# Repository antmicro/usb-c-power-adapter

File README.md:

# USB-C Power Delivery Adapter

Copyright (c) 2025 [Antmicro](https://www.antmicro.com)

## Overview

The USB-C Power Delivery Adapter is a module providing **12V 55W** continuous power output from a single [**USB-C PD**](https://www.usb.org/usb-charger-pd) power supply. 
The board was designed as a power option for [Antmicro's Thunderbolt to GPU Adapter](https://openhardware.antmicro.com/boards/thunderbolt-gpu-adapter/?tab=features) in stand-alone operation.

The design files were prepared in [KiCad 9.x](https://www.kicad.org/).

## Key features
* **12V 55W** output 
* Up to **75 Watts** achievable with active cooling
* Vishay [SIC477](https://www.vishay.com/docs/77113/sic47x.pdf) voltage buck regulator, operating at 94% efficiency
* STMicroelectronics [STUSB4500](https://www.mouser.com/datasheet/2/389/dm00489312-1799262.pdf) USB Power Delivery sink controller
* Additional **+5V** and **+3.3V** DC/DC converters delivering up to 500mA of continuous output current
* [QWIIC](https://www.sparkfun.com/qwiic) connector for programming the Power Delivery profile
* [Molex Nano-Fit](https://www.molex.com/en-us/products/connectors/wire-to-board-connectors/nano-fit-connectors) output connector
* Overload and overtemperature protection

## Configuration
To operate properly, the PD sink controller must be first programmed.\
The [QWIIC](https://www.sparkfun.com/qwiic) connector is dedicated for I2C connection with STUSB4500.\
Programming instructions and tools can be found on the [manufacturer's website](https://www.st.com/en/interfaces-and-transceivers/stusb4500.html#overview).

Below, you can find the recommended profile for the PD sink:
```console
PDO1: 5V (+15%/-5%), 1.5A
PDO2: 20.0V (+10%/-20%), 3.0A
PDO3: 20.0V (+10%/-20%), 4.5A
PDO Number: 3
Flex Current: 2.0
External Power: False
USB Communication Capable: False
Configuration OK GPIO: 2
GPIO Control: 1
Enable Power Only Above 5V: False
Request Source Current: False
Factory Default: False
```

## Operation
The USB-C Power Delivery Adapter must be powered from a USB PD power supply with the following features:
  * capable of delivering **20 V** 
  * power rating exceeding the required load ( >60 W PD supply recommended)
  * supporting at least one of the programmed PD profiles

## Project structure
* `/.` -  contains the KiCad project files, the license and this README file
* `/doc`- contains schematics in PDF format
* `/assets` - contains visual assets for showcasing this design on [Open Hardware Portal](https://openhardware.antmicro.com).

## License
The project is published under the [Apache 2.0](/LICENSE) license.

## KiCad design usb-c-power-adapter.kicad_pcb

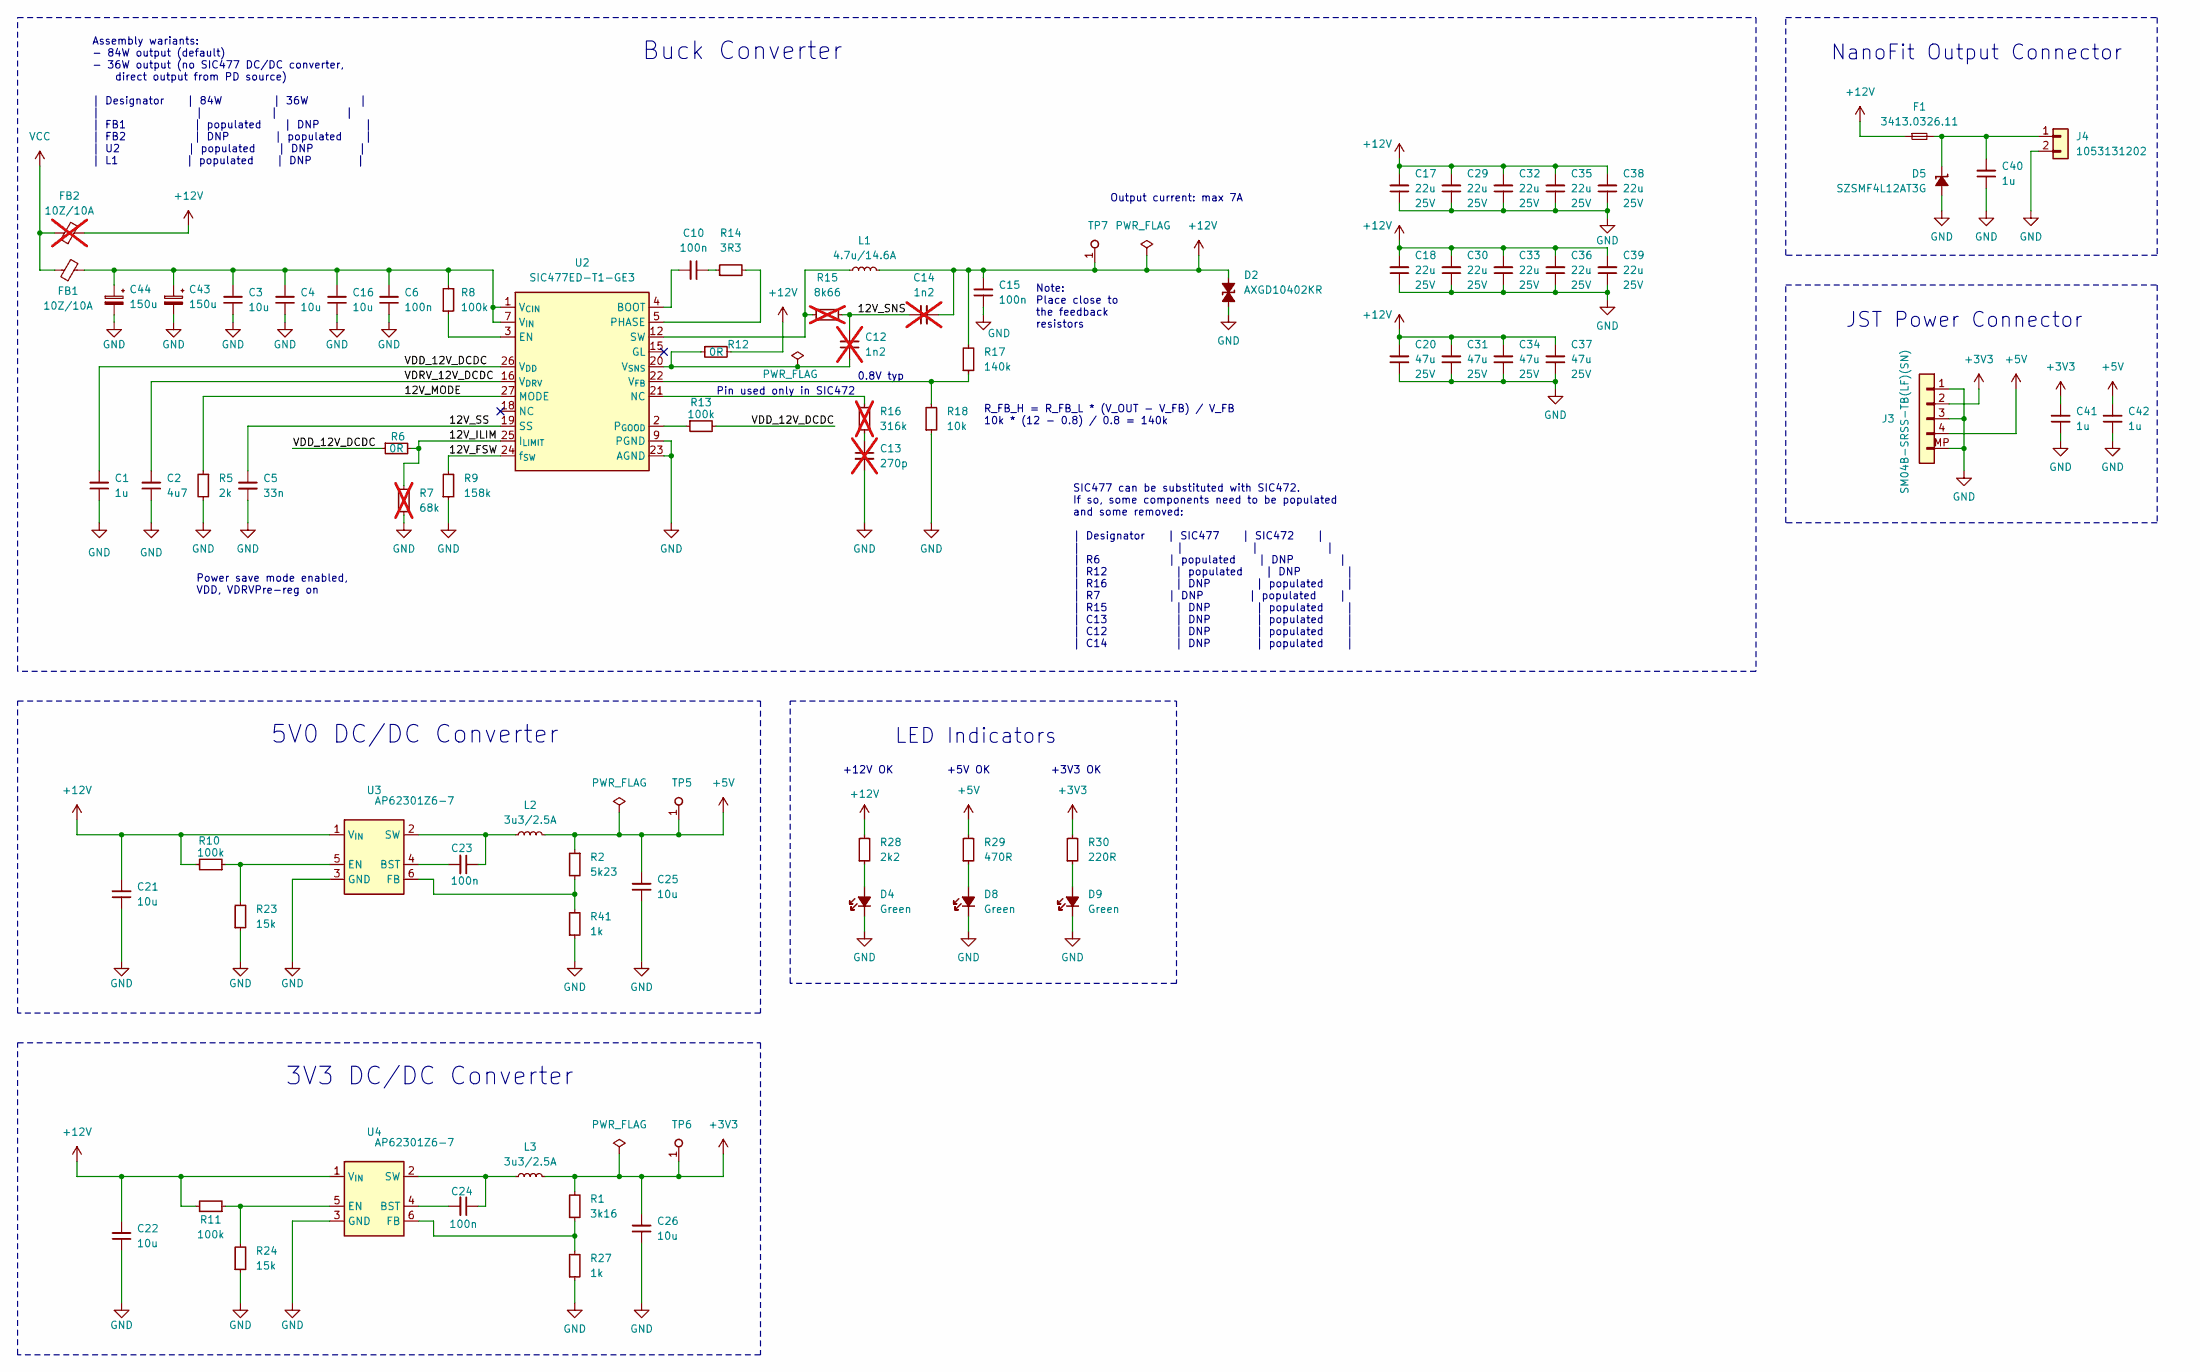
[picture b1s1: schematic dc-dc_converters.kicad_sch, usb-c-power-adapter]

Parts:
C1, C40, C41, C42: C_1u_25V_0402; C_0402_1005Metric; Voltage 25V; MPN GRM155R61E105KE11J
C2: C_4u7_25V_0402; C_0402_1005Metric; Voltage 25V; MPN GRM155C61E475ME15J
C3, C4, C16: C_10u_0805_35V; C_0805_2012Metric; Voltage 35V; MPN GRM21BR6YA106KE43L
C5: C_33n_0402; C_0402_1005Metric; MPN GCM155R71E333KA55D
C6, C10, C15, C23, C24: C_100n_50V_X8L_0402; C_0402_1005Metric; Voltage 50V; MPN GCM155L8EH104KE07D
C12, C14: C_1n2_50V_0402; C_0402_1005Metric; Voltage 50V; MPN GCM155R71H122KA37D; not fitted
C13: C_270p_25V_0402; C_0402_1005Metric; Voltage 25V; MPN C0402C271J3GAC7867; not fitted
C17, C18, C29, C30, C32, C33, C35, C36, C38, C39: C_22u_25V_0805; C_0805_2012Metric; Voltage 25V; MPN CL21A226MAYNNNE
C20, C31, C34, C37: C_47u_25V_1206; C_1206_3216Metric; Voltage 25V; MPN C3216X5R1E476M160AC
C21, C22, C25, C26: C_10u_25V_0603; C_0603_1608Metric; Voltage 25V; MPN C1608X5R1E106M080AC
C43, C44: C_Pol_150u_30V_Vishay-T59-EE; C_Pol_Vishay-T59-EE; Voltage 30V; MPN T59EE157M030C0075
D2: AXGD10402KR; D_0402_1005Metric; MPN AXGD10402KR
D4, D8, D9: LED_G_0603_LG_L29K-G2J1-24-Z; LED_0603_1608Metric_G; MPN LG L29K-G2J1-24-Z
D5: SZSMF4L12AT3G; SOD-123FL; MPN SZSMF4L12AT3G
F1: F_7A_1206; F_1206_3216Metric; MPN 3413.0326.11
FB1: FB_10Z_10A_WE-MPSB_1206; FB_1206_3216Metric; MPN 74279221100
FB2: FB_10Z_10A_WE-MPSB_1206; FB_1206_3216Metric; MPN 74279221100; not fitted
J3: JST_SH_1x4_SM04B-SRSS-TB-LF-SN; Conn_JST_SH_1x4_SM04B-SRSS-TB-LF-SN; MPN SM04B-SRSS-TB(LF)(SN)
J4: Molex_Nano-Fit_1x2_1053131202; Conn_Molex_Nano-Fit_1x2_1053131102; MPN 1053131202
L1: L_4u7_14.6A_Abracon-Q8080; L_Abracon_ASPIAIG-Q8080; MPN ASPIAIG-Q8080-4R7M-T
L2, L3: L_3u3_2.5A_1008; L_1008_2520Metric; MPN TFM252012ALMA3R3MTAA
R1: R_3k16_0402; R_0402_1005Metric; Tolerance 1%; MPN RC0402FR-073K16L
R2: R_5k23_0402; R_0402_1005Metric; Tolerance 1%; MPN RC0402FR-075K23L
R5: R_2k_0402; R_0402_1005Metric; Tolerance 1%; MPN CR0402-FX-2001GLF
R6, R12: R_0R_0402; R_0402_1005Metric; MPN ERJ2GE0R00X
R7: R_68k_0402; R_0402_1005Metric; Tolerance 1%; MPN CR0402-FX-6802GLF; not fitted
R8, R10, R11, R13: R_100k_0402; R_0402_1005Metric; Tolerance 1%; MPN CR0402-FX-1003GLF
R9: R_158k_0402; R_0402_1005Metric; Tolerance 1%; MPN CR0402-FX-1583GLF
R14: R_3R3_0402; R_0402_1005Metric; Tolerance 1%; MPN CR0402-FX-3R30GLF
R15: R_8k66_0402; R_0402_1005Metric; Tolerance 1%; MPN CR0402-FX-8661GLF; not fitted
R16: R_316k_0402; R_0402_1005Metric; Tolerance 1%; MPN CR0402-FX-3163GLF; not fitted
R17: R_140k_0.1%_0402; R_0402_1005Metric; Tolerance 0.1%; MPN RT0402BRD07140KL
R18: R_10k_0.1%_0402; R_0402_1005Metric; Tolerance 0.1%; MPN CRT0402-BY-1002GLF
R23, R24: R_15k_0402; R_0402_1005Metric; Tolerance 1%; MPN CR0402-FX-1502GLF
R27, R41: R_1k_0402; R_0402_1005Metric; Tolerance 1%; MPN CR0402-FX-1001GLF
R28: R_2k2_0402; R_0402_1005Metric; Tolerance 1%; MPN CR0402-FX-2201GLF
R29: R_470_0402; R_0402_1005Metric; Tolerance 1%; MPN CR0402-FX-4700GLF
R30: R_220R_0402; R_0402_1005Metric; Tolerance 1%; MPN CR0402-FX-2200GLF
TP5, TP6, TP7: TP_0.75mm_SMD; TP_SMD_0.75mm
U2: SIC477ED-T1-GE3; SIC47XED-T1-GE3; MPN SIC477ED-T1-GE3
U3, U4: AP62301Z6-7; SOT-563; MPN AP62301Z6-7

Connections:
+3V3: C26.2, C41.2, J3.2, L3.2, R1.2, R30.2, TP6.1; also elsewhere on the board
+5V: C25.2, C42.2, J3.4, L2.2, R2.1, R29.2, TP5.1; also elsewhere on the board
+12V: C14.2, C15.2, C17.2, C18.2, C20.2, C21.2, C22.2, C29.2, C30.2, C31.2, C32.2, C33.2, C34.2, C35.2, C36.2, C37.2, C38.2, C39.2, D2.2 (A), F1.1, FB2.2, L1.2, R10.2, R11.2, R12.2, R17.2, R28.2, TP7.1, U3.1 (V_{IN}), U4.1 (V_{IN})
/DC-DC Converters/12V_FSW: R9.2, U2.24 (f_{SW})
/DC-DC Converters/12V_ILIM: R6.2, R7.2, U2.25 (I_{LIMIT})
/DC-DC Converters/12V_MODE: R5.1, U2.27 (MODE)
/DC-DC Converters/12V_SNS: C12.2, C14.1, R15.2
/DC-DC Converters/12V_SS: C5.1, U2.19 (SS)
/DC-DC Converters/VDD_12V_DCDC: C1.2, R6.1, R13.2, U2.26 (V_{DD})
/DC-DC Converters/VDRV_12V_DCDC: C2.2, U2.16 (V_{DRV})
GND: C1.1, C2.1, C3.1, C4.1, C5.2, C6.1, C13.2, C15.1, C16.1, C17.1, C18.1, C20.1, C21.1, C22.1, C25.1, C26.1, C29.1, C30.1, C31.1, C32.1, C33.1, C34.1, C35.1, C36.1, C37.1, C38.1, C39.1, C40.1, C41.1, C42.1, C43.2, C44.2, D2.1 (C), D4.1 (C), D5.2 (A), D8.1 (C), D9.1 (C), J3.1, J3.3, J3.MP, J4.2, R5.2, R7.1, R9.1, R18.1, R23.1, R24.1, R27.1, R41.1, U2.9 (PGND), U2.10 (PGND), U2.11 (PGND), U2.17 (PGND), U2.23 (AGND), U2.28 (AGND), U3.3 (GND), U4.3 (GND); also elsewhere on the board
unnamed: C10.1, R14.1
unnamed: C13.1, R16.2
unnamed: D4.2 (A), R28.1
unnamed: C40.2, D5.1 (C), F1.2, J4.1
unnamed: D8.2 (A), R29.1
unnamed: D9.2 (A), R30.1
unnamed: L1.1, R15.1, U2.12 (SW), U2.13 (SW), U2.14 (SW)
unnamed: R14.2, U2.5 (PHASE), U2.6 (PHASE)
unnamed: R16.1, U2.21 (NC)
unnamed: C10.2, U2.4 (BOOT)
unnamed: R8.1, U2.3 (EN)
unnamed: R13.1, U2.2 (P_{GOOD})
unnamed: C3.2, C4.2, C6.2, C16.2, C43.1, C44.1, FB1.2, R8.2, U2.1 (V_{CIN}), U2.7 (V_{IN}), U2.8 (V_{IN})
unnamed: R17.1, R18.2, U2.22 (V_{FB})
unnamed: C12.1, R12.1, U2.20 (V_{SNS})
unnamed: C23.2, U3.4 (BST)
unnamed: R10.1, R23.2, U3.5 (EN)
unnamed: R2.2, R41.2, U3.6 (FB)
unnamed: C23.1, L2.1, U3.2 (SW)
unnamed: C24.2, U4.4 (BST)
unnamed: R11.1, R24.2, U4.5 (EN)
unnamed: R1.1, R27.2, U4.6 (FB)
unnamed: C24.1, L3.1, U4.2 (SW)
VCC: FB1.1, FB2.1; also elsewhere on the board

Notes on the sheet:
Note: Place close to the feedback resistors
Power save mode enabled, VDD, VDRVPre-reg on
+5V OK
R_FB_H = R_FB_L * (V_OUT - V_FB) / V_FB 10k * (12 - 0.8) / 0.8 = 140k
0.8V typ
+12V OK
Buck Converter
SIC477 can be substituted with SIC472. If so, some components need to be populated and some removed: | Designator | SIC477 | SIC472 | | | | | | R6 | populated | DNP | | R12 | populated | DNP | | R16 | DNP | populated | | R7 | DNP | populated | | R15 | DNP | populated | | C13 | DNP | populated | | C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
LED Indicators
5V0 DC/DC Converter
Pin used only in SIC472
3V3 DC/DC Converter
Assembly wariants: - 84W output (default) - 36W output (no SIC477 DC/DC converter, direct output from PD source) | Designator | 84W | 36W | | | | | | FB1 | populated | DNP | | FB2 | DNP | populated | | U2 | populated | DNP | | L1 | populated | DNP |
JST Power Connector
NanoFit Output Connector
Output current: max 7A
+3V3 OK

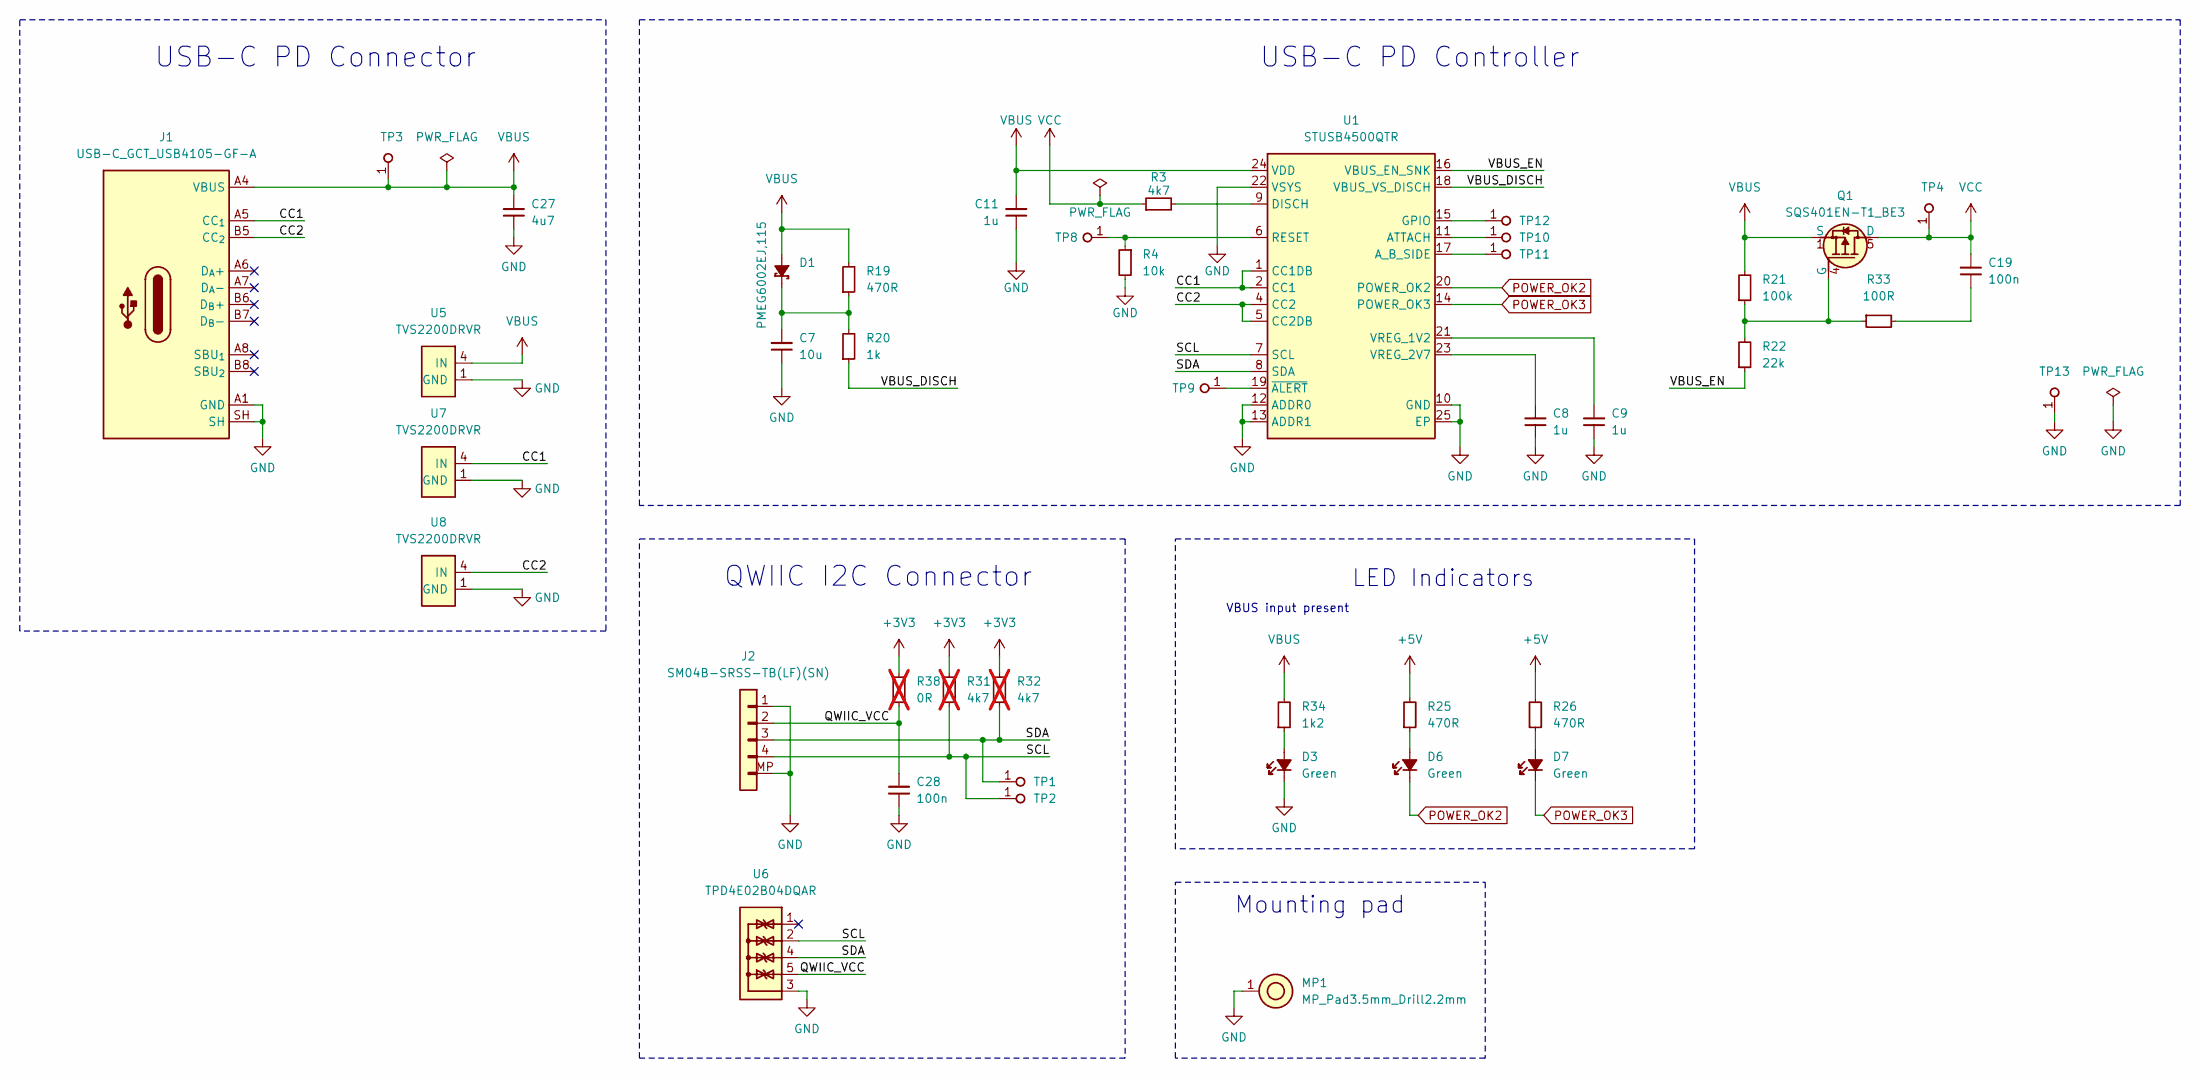
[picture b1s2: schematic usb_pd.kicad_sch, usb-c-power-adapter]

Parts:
C7: C_10u_0805_35V; C_0805_2012Metric; Voltage 35V; MPN GRM21BR6YA106KE43L
C8, C9, C11: C_1u_25V_0402; C_0402_1005Metric; Voltage 25V; MPN GRM155R61E105KE11J
C19, C28: C_100n_50V_X8L_0402; C_0402_1005Metric; Voltage 50V; MPN GCM155L8EH104KE07D
C27: C_4u7_25V_0402; C_0402_1005Metric; Voltage 25V; MPN GRM155C61E475ME15J
D1: PMEG6002EJ,115; D_SOD-323F; MPN PMEG6002EJ,115
D3, D6, D7: LED_G_0603_LG_L29K-G2J1-24-Z; LED_0603_1608Metric_G; MPN LG L29K-G2J1-24-Z
J1: USB-C_GCT_USB4105-GF-A; USB-C_Receptacle_GCT_USB4105-GF-A; MPN USB4105-GF-A
J2: JST_SH_1x4_SM04B-SRSS-TB-LF-SN; Conn_JST_SH_1x4_SM04B-SRSS-TB-LF-SN; MPN SM04B-SRSS-TB(LF)(SN)
MP1: MP_Pad3.5mm_Drill2.2mm
Q1: SQS401EN-T1_BE3; Vishay_PowerPAK_1212-8_Single; MPN SQS401EN-T1_BE3
R3: R_4k7_0603; R_0603_1608Metric; Tolerance 1%; MPN CR0603-FX-4701ELF
R4: R_10k_0402; R_0402_1005Metric; Tolerance 1%; MPN CR0402-FX-1002GLF
R19, R25: R_470R_0402; R_0402_1005Metric; Tolerance 1%; MPN CR0402-FX-4700GLF
R20: R_1k_0402; R_0402_1005Metric; Tolerance 1%; MPN CR0402-FX-1001GLF
R21: R_100k_0402; R_0402_1005Metric; Tolerance 1%; MPN CR0402-FX-1003GLF
R22: R_22k_0402; R_0402_1005Metric; Tolerance 1%; MPN CR0402-FX-2202GLF
R26: R_470_0402; R_0402_1005Metric; Tolerance 1%; MPN CR0402-FX-4700GLF
R31, R32: R_4k7_0402; R_0402_1005Metric; Tolerance 1%; MPN CR0402-FX-4701GLF; not fitted
R33: R_100R_0402; R_0402_1005Metric; Tolerance 1%; MPN CR0402-FX-1000GLF
R34: R_1k2_0402; R_0402_1005Metric; Tolerance 1%; MPN CR0402-FX-1201GLF
R38: R_0R_0402; R_0402_1005Metric; MPN ERJ2GE0R00X; not fitted
TP1, TP2, TP3, TP4, TP8, TP9, TP10, TP11, TP12, TP13: TP_0.75mm_SMD; TP_SMD_0.75mm
U1: STUSB4500_QFN; QFN-24-1EP_4x4mm_P0.5_EP2.1x2.1mm; MPN STUSB4500QTR
U5, U7, U8: TVS2200DRVR; WSON-6-1EP_2x2mm_P0.65mm; MPN TVS2200DRVR
U6: TPD4E02B04DQA; USON-10_2.5x1mm_P0.5mm; MPN TPD4E02B04DQAR

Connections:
+3V3: R31.2, R32.2, R38.2; also elsewhere on the board
+5V: R25.2, R26.2; also elsewhere on the board
/USB PD/CC1: J1.A5 (CC_{1}), U1.1 (CC1DB), U1.2 (CC1), U7.4 (IN), U7.5 (IN), U7.6 (IN)
/USB PD/CC2: J1.B5 (CC_{2}), U1.4 (CC2), U1.5 (CC2DB), U8.4 (IN), U8.5 (IN), U8.6 (IN)
/USB PD/QWIIC_VCC: C28.2, J2.2, R38.1, U6.5, U6.6
/USB PD/SCL: J2.4, R31.1, TP2.1, U1.7 (SCL), U6.2, U6.9
/USB PD/SDA: J2.3, R32.1, TP1.1, U1.8 (SDA), U6.4, U6.7
/USB PD/VBUS_DISCH: R20.1, U1.18 (VBUS_VS_DISCH)
/USB PD/VBUS_EN: R22.1, U1.16 (VBUS_EN_SNK)
GND: C7.1, C8.1, C9.1, C11.1, C27.1, C28.1, D3.1 (C), J1.A1 (GND), J1.A12 (GND), J1.B1 (GND), J1.B12 (GND), J1.SH, J2.1, J2.MP, MP1.1, R4.2, TP13.1, U1.10 (GND), U1.12 (ADDR0), U1.13 (ADDR1), U1.22 (VSYS), U1.25 (EP), U5.1 (GND), U5.2 (GND), U5.3 (GND), U5.7 (GND), U6.3, U6.8, U7.1 (GND), U7.2 (GND), U7.3 (GND), U7.7 (GND), U8.1 (GND), U8.2 (GND), U8.3 (GND), U8.7 (GND); also elsewhere on the board
unnamed: C19.1, R33.2
unnamed: C7.2, D1.1 (C), R19.1, R20.2
unnamed: D3.2 (A), R34.1
unnamed: D6.2 (A), R25.1
unnamed: D7.2 (A), R26.1
unnamed: Q1.4 (G), R21.1, R22.2, R33.1
unnamed: TP10.1, U1.11 (ATTACH)
unnamed: TP11.1, U1.17 (A_B_SIDE)
unnamed: R3.2, U1.9 (DISCH)
unnamed: TP12.1, U1.15 (GPIO)
unnamed: R4.1, TP8.1, U1.6 (RESET)
unnamed: C9.2, U1.21 (VREG_1V2)
unnamed: C8.2, U1.23 (VREG_2V7)
unnamed: TP9.1, U1.19 (~ALERT)
POWER_OK2: D6.1 (C), U1.20 (POWER_OK2)
POWER_OK3: D7.1 (C), U1.14 (POWER_OK3)
VBUS: C11.2, C27.2, D1.2 (A), J1.A4 (VBUS), J1.A9 (VBUS), J1.B4 (VBUS), J1.B9 (VBUS), Q1.1 (S), Q1.2 (S), Q1.3 (S), R19.2, R21.2, R34.2, TP3.1, U1.24 (VDD), U5.4 (IN), U5.5 (IN), U5.6 (IN)
VCC: C19.2, Q1.5 (D), R3.1, TP4.1; also elsewhere on the board

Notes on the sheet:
USB-C PD Controller
LED Indicators
VBUS input present
Mounting pad
QWIIC I2C Connector
USB-C PD Connector

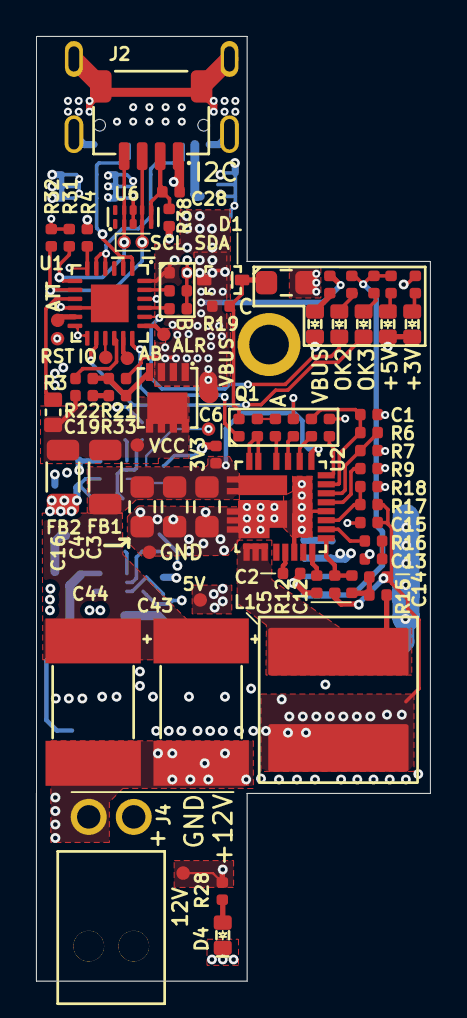
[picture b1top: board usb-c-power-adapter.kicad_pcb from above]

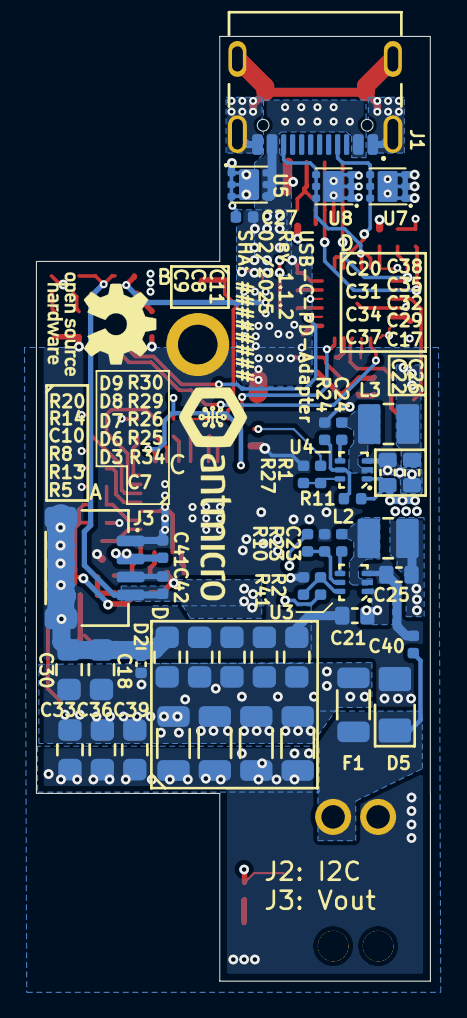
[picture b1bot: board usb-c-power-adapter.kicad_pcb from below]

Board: 4 copper layers, 21.9 x 52.5 mm, 124 parts (46 on the bottom side), 59 nets.

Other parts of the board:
N1: antmicro_logo; antmicro-logo_scaled_12mm_silk
N2: oshw_logo; OSHW-Logo_5.7x6mm_SilkScreen

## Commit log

2024-03-25 [#57006] Initial comit
2024-03-25 [#57006] Add USB-C connector
2024-03-25 [#57006] Add qwiic connector
2024-03-25 [#57006] Add Buck converter
2024-03-25 [#57006] Add USB PD controller
2024-03-25 [#57006] Update schematic
2024-03-27 [#57006] Swap I2C lines
    Align to grid
    Add notes
2024-03-27 [#57006] Change buck converter to SIC477ED-T1-GE3, WIP
2024-03-27 [#57006] Change feedback resistors
2024-03-28 [#57006] Update connections
    Change nanofit connector
    Change feedback resistors to 0.1%
2024-03-28 [#57006] Change C13, C14, C16
    Use capactitors rated for higher voltages
2024-03-28 [#57006] Add 3v3 and 5v dcdc converters
2024-03-28 [#57006] Move connectors to separate sheet
2024-03-28 [#57006] Change C17, R25, R26
    Improve connections
2024-03-28 [#57006] Add assembly variant selector
2024-03-28 [#57006] Change L1
2024-03-29 [#57006] Add a TVS diode on output
    Move power components to a new sheet
2024-03-29 [#57006] Align components to grid
2024-03-29 [#57006] Reorganize structure
2024-03-29 [#57006] Clean ERC warnings
2024-03-29 [#57006] Add LEDs on POWER_GOOD signals
2024-03-29 [#57006] Update symbols
2024-04-02 [#57006] Rename power supply sheet
2024-04-02 [#57006] Add web address
2024-04-02 [#57006] Add full date
2024-04-02 [#57006] Add 0R resistor on 3v3 qwiic
2024-04-02 [#57006] Add LEDs on 3v3 and 5v output
2024-04-02 [#57006] Improve SIC472/SIC477 assembly variants note
    Align components
2024-04-02 [#57006] Change power output variant selector
    Use ferrites instead of resistors
2024-04-02 [#57006] Remove buses to improve readability
    Change output power block's name
2024-04-02 [#57006] Change feedback resistors for U3, U4
2024-04-02 [#57006] Change D5 to SZSMF4L12AT3G
2024-04-02 [#57006] Remove fuse on VBUS input
2024-04-02 [#57006] Change diodes' resistors
    Decrease current
2024-04-02 [#57006] Fix wrong power label
    Add +12V testpoint
2024-04-02 [#57006] Remove R11, C8
2024-04-02 [#57006] Add val field to F1
2024-04-02 [#57006] Change EN resistors for U3, U4
2024-04-02 [#57006] Change R20 to 1k
    Move some components to improve readability
2024-04-04 [#57006] Mark R31, R32 as non DNP
    To avoid I2C lines floating
2024-04-04 [#57006] Add logos
2024-04-04 [#57006] Change capacitors to higher voltage ratings
    Homogenize capacitors (to not use multiple versions of the same params)
2024-04-04 [#57006] Change Rfsw to 158k
2024-04-04 [#57006] Change R3 to 0603
2024-04-04 [#57006] Change U3 U4 to SOT-563
2024-04-04 [#57006] Fix POWER_OK2, POWER_OK3 LEDs
2024-04-04 [#57006] Change D2 to AXGD10402KR
2024-04-04 [#57006] Add more testpoints
2024-04-04 [#57006] Change R7 to 68k
2024-04-04 [#57006] Add tranzistor on D3
    PD input present LED
2024-04-04 [#57006] Remove tranzistor on D3
    Change LED resistor's value
2024-04-04 [#57006] Add TVS2200DRVR on PD input
2024-04-04 [#57006] Remove PGOOD label
2024-04-04 [#57006] Change L2 and L3
2024-04-04 [#57006] Update SIC477 from library
    Add note about NC pin 21
2024-04-04 [#57006] Change C17, C18, C20 to 25V capacitors
2024-04-04 [#57006] Add 100u DNP capacitor
2024-04-04 [#57006] Update PCB from schematics
2024-08-01 [#57764] Arrange silkscreen
2024-08-01 [#57225] Fix drc
2024-08-01 [#57255] Finish routing
2024-08-01 [#57225] Placement of buck converter
2024-08-01 [#57225] Add dimensions
2024-08-01 [#57225] Improve Vbus, add output caps to layout
2024-08-01 [[#57225] Update board dimensions
2024-08-01 [#57225] Add MolexNano Fit
2024-08-01 [#57225] Change L2, L3
2024-08-01 [#57225] Place QWIIC Connector
2024-08-01 [#57225] Modify capacitors on schematic
2024-08-01 [#57764] Add pin 1 marking to the silkscreen frames
2024-08-01 [#57225] Fix outline
2024-08-01 [#57225] Finish placement
2024-08-01 [#57225] Rotate U5
2024-08-01 [#57225] Place QWIIC power connector
2024-08-01 [#57225] Update PCB
2024-08-01 [#57225] Update board edge
2024-08-01 [#57225] Add usb-c connector
2024-08-01 [#57255] Add power planes
2024-08-01 [#57764] Fix TP8
    Connect to RESET pin
2024-08-01 [#57225] Import dxf
2024-08-01 [#57225] Improve silkscreen
2024-08-01 [#57764] Improve test points routing
    Use wider routes
2024-08-01 [#57607] Update symbols from library
2024-08-01 [#57764] Connect MP1 to GND
    Resolve DRC errors
2024-08-01 [#57764] ADD GND testpoint
2024-08-01 [#57225] Placement
2024-08-01 [#57225] Add mounting pad
2024-08-01 [#57225] All signals routed, silkscreen TODO
2024-08-01 [#57764] Change min text height to 0.7
2024-08-01 [#57225] Place 5V/3v3 SMPS
2024-08-01 [#57225] Component placement
2024-08-01 [#57225] Change C17, C18, C20
2024-08-01 [#57225] Route DCDC and power paths
2024-08-01 [#57764] Fix DRC
    Arrange test points
2024-08-01 [#57225] Fix board dimensions
2024-08-01 [#57607] Update STUSB45 symbol
2024-08-01 [#57764] Unify fonts
2024-08-01 [#57764] Properly save the exclusions
2024-08-01 [#59888] Fix spelling, delete useless info
2024-08-01 [#59888] Fix a typo
2024-08-01 [#57225] Replace resistor from library
2024-08-01 [#57607] Update symbols and footprints
    Update PCB from schematics
2024-08-01 Edit README
2024-08-01 [#61462] Replace C7 with C_10u_0805_35V
2024-08-01 [#57966] Updated R20 from symbol library
2024-08-01 [#57225] Update symbols/footprints
2024-08-01 [#61462] Initial placement
2024-08-01 Update render
2024-08-01 [#57966] Updated R20, R25, R31 and R32 on PCB
2024-08-01 [#57225] Remove vias from logos
2024-08-01 [#57225] Update PRO file
2024-08-01 [#61462] Route all of the signals Initially arrange silkscreen
2024-08-01 [#57973] Add render
2024-08-01 [#57973] Add operation paragraph
2024-08-01 [#57225] Improve power path
2024-08-01 [#57225] Improve grounding
2024-08-01 [#57973] Add readme, WIP
2024-08-01 [#61462] Add two 150u capacitors on U2 input
2024-08-01 [#57973] Add license
2024-08-01 [#59888] Improve readme
2024-08-01 [#57225] Add antmicro logos
2024-08-01 [#57607] Clean DRC and ERC
2024-08-01 [#57973] Improve readme
2024-08-01 [#59888] Restore license
2024-08-01 Add more information to operation paragraph
2024-08-01 [#57973] Add schematic in pdf format
2024-08-01 [#57225] Solve DRC
2024-08-01 [#62611] Remove non valid note on schematic
2024-08-01 [#61462] Update ERC and DRC violation severity
2024-08-01 [#61462] Bump revision to 1.1.0
2024-08-01 [#62611] Bump revision to 1.1.0 on PCB drawing frame
    Update date
2024-08-01 [#61462] Update symbols from library and resolve ERC issues
2024-08-01 [#61462] Update PCB from schematics, update footprints from library, resolve DRC
2024-08-01 [#61462] Change L1 to Abracon ASPIAIG-Q8080-4R7M-T
    Update C43, C44 footprints
    Resolve DRCs
2024-08-19 [#62611] Improve readability near C5
2024-08-19 [#62611] Improve assembly variants note
2024-08-19 [#62611] Align designators Improve readability Update symbols' fields' visibility from library
2024-08-19 [#62611] Run kmake DNP
2024-08-19 [#63438] README: review
2024-08-19 [#62611] Add stackup.csv
2024-08-19 [#62611] Fix wrong value fields for R26, R29
2024-08-19 [#62611] Add data.json
2024-08-19 [#62611] Increase L1-Pad1 track width Rearrange and reroute RC between L1 and U2
2024-08-19 Rename schematic in PDF format
2024-08-19 [#62611] Update render for readme file
2024-08-19 [#62611] Fix OHP assets
2024-08-19 [#62611] Add OHP assets
2024-08-19 [#62611] Arrange silkscreen Add I2C Vout silkscreen indicators
2024-08-19 [#63438] Add manufacturer name to Nano-Fit connector
2024-08-19 [#63438] Update render used in readme
2024-08-19 [#63438] Regenerate assets
2025-02-04 Add .ci.yml
2025-02-04 Save in KiCad 8
2025-02-04 [#72550] Update C43 C44 tantal capacitors MPNs
2025-02-05 [#72550] Update symbols from library (Remove DNP, VSD_Class and Public fields)
2025-02-05 [#72550] Change logos to footprint not in the sch, Update pcb from sch
2025-02-05 [#72550] Update and clenup DRCs
2025-02-05 [#72550] Bump rev to 1.1.1, update date
2025-02-05 [#72550] Better allign sch designators
2025-02-05 [#72550] Update README
2025-02-05 [#72550] Rename project to lower case letters
2025-02-05 [#72550] Upload assets
2025-02-06 [#72550] Sync Not in Bom attributes
2025-02-06 [#72550] Update footprint from lib
2025-02-06 [#72550] Update stackup
2025-02-06 [#72550] Update assets
2025-06-24 [#79385] Replace Molex, set R8 as dnp on schematic
2025-06-24 [#79385] Replace molex on pcb
2025-06-24 [#79385] Update gitignore
2025-06-24 [#79385] Update DNP
2025-06-24 [#79385] Fix DRC
2025-06-24 [#79385] Bump revision
2025-06-24 [#79385] Update .ci.yml
2025-06-24 [#79385] Update assets
2025-07-29 [#79385] Remove assets folder
2025-07-29 [#79385] Update components from lib
2025-07-29 [#79385] Update README photo
2025-07-29 [#79385] Update KiCad version in README

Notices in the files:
parts and their libraries:
License: Apache-2.0
